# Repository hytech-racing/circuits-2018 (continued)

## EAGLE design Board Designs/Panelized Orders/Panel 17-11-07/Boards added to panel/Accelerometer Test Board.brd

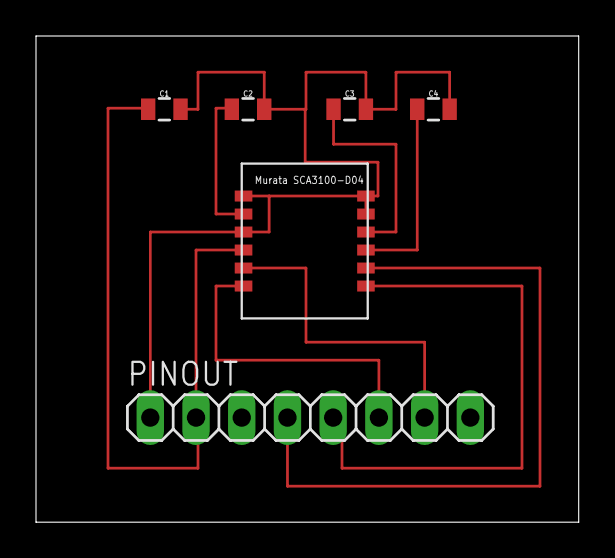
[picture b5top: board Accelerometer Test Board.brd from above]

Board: 2 copper layers, 30.1 x 27.0 mm, 6 parts (0 on the bottom side), 9 nets.

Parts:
C1, C2, C3, C4: 130 nF; 0805
PINOUT: 1X08
U$1: SCA3100-D04

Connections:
GND: C1.2, C2.2, C3.2, C4.2, PINOUT.1, U$1.AVSS, U$1.DVSS, U$1.EMC_GND, U$1.RESERVED
unnamed: C2.1, U$1.A_EXTC
unnamed: C3.1, U$1.D_EXTC
unnamed: C4.1, U$1.DVIO
unnamed: PINOUT.5, U$1.MOSI
unnamed: PINOUT.4, U$1.SCK
unnamed: PINOUT.7, U$1.CSB
unnamed: PINOUT.6, U$1.MISO
VDD: C1.1, PINOUT.2, U$1.VDD

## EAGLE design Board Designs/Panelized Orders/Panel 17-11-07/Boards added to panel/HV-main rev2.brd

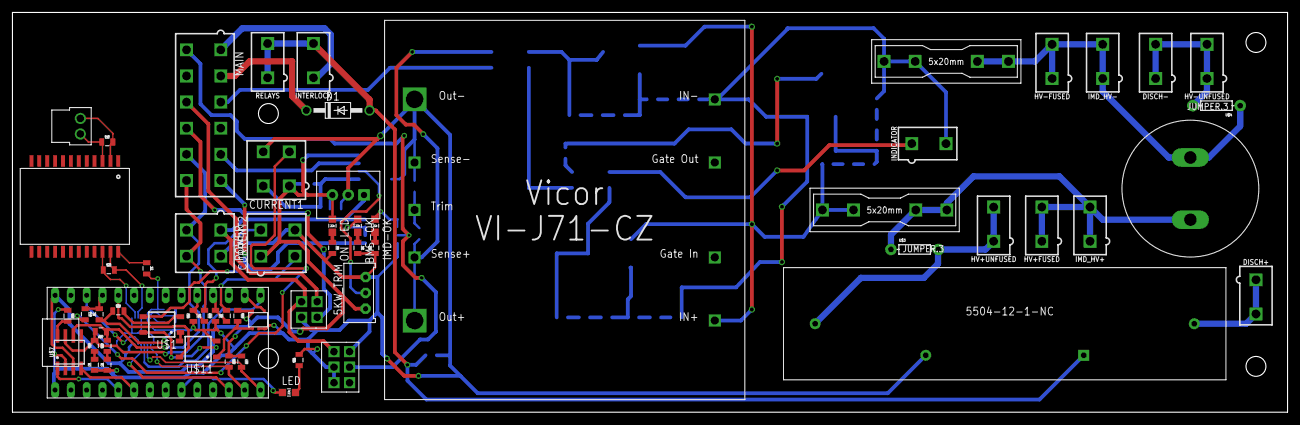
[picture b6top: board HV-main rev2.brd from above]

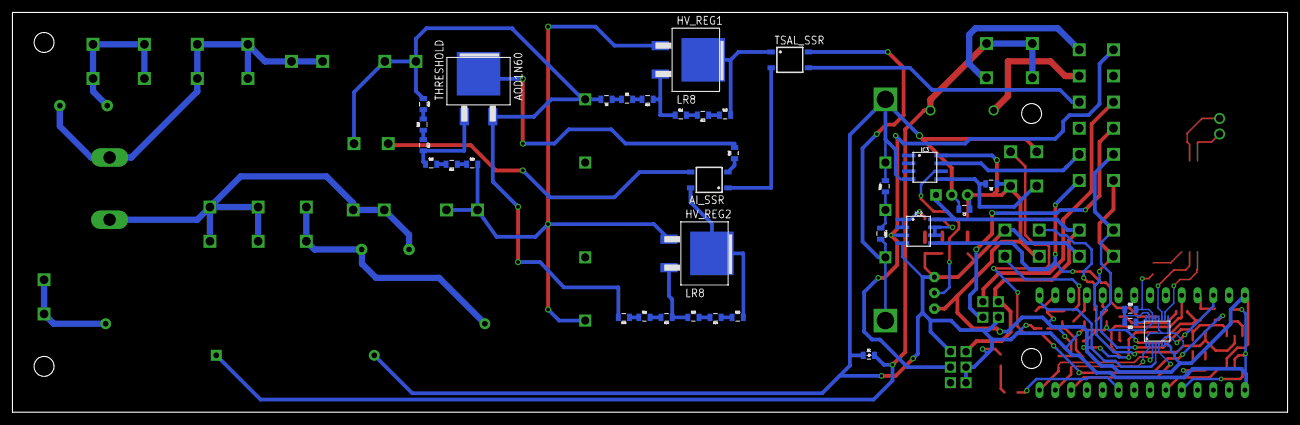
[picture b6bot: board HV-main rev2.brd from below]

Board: 2 copper layers, 205.0 x 64.3 mm, 95 parts (34 on the bottom side), 81 nets.

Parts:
5KW_TRIM: TRIMPOT_3296
AI_SSR: CPC1002N; SOP04
BMS-OK: LED-805
C1: 220uF; LLS2V221MELZ
C3: 1uF; 0805
C4: 27pF; 0805
C8, C9: 560pF; 0805
CURRENT1, CURRENT2: MINIFIT_5566-4
D1: DIODE; DO-41
D2: DIODE0805; 0805_D
DISCH+: DISCHARGE+; MINIFIT_5566-2
DISCH-: DISCHARGE -; MINIFIT_5566-2
EM: CONNECTOR-4; NANO-FIT_VERTICAL-4
FUSE, FUSE1: 1A; 0751.0110
HV+FUSED: MINIFIT_5566-2
HV+UNFUSED: FSAE; MINIFIT_5566-2
HV-FUSED: MINIFIT_5566-2
HV-UNFUSED: FSAE; MINIFIT_5566-2
HV_REG1, HV_REG2: LR8; TO-252
IC1: TO-220
IC2, IC3: NE5532SOIC; SOIC-08
IMD: CONNECTOR-6; NANO-FIT_VERTICAL-6
IMD-OK: LED-805
IMD_HV+: MINIFIT_5566-2
IMD_HV-: MINIFIT_5566-2
INDICATOR: MINIFIT_5566-2
INTERLOCK: MINIFIT_5566-2
ISOSPI: CONNECTOR-2; NANO-FIT_VERTICAL-2
LED: LED-805
MAIN: MINIFIT_5566-12
ON-LED: LED-805
POWER: MINIFIT_5566-4
R1, R2, R26, R30, R33, R34, R44: 1k; 0805
R3, R4, R31: 0805
R5, R28, R29, R40: 100; 0805
R6: 10k; 0805
R7, R11, R12, R13, R23, R24, R25, R32, R36, R37, R43: 2k; 0805
R8, R9, R10: 8.2k; 0805
R14, R15, R16: 500k; 0805
R17, R18, R19: 40k; 0805
R20, R21, R22: 20k; 0805
R27, R35: 120; 0805
R38: 68; 0805
R39: 200; 0805
RELAYS: MINIFIT_5566-2
THRESHOLD: AOD1N60; TO-252
TRIM+: 0805
TRIM-: 0805
TSAL_SSR: CPC1002N; SOP04
U$1, U$11: SOP04
U$2: SM51589PEL
U$3, U$4: JUMPER.3; AXIAL-0.3
U$5: HV_DCDC_VI-J71-CZ
U$7: MCP2551; SOIC-08
U$8: LTC6820; MSOP-16
U$9: TEENSY_3.2_SIMPLE
U$10: STWD100; SOT23-5
U$12: 5504-12-1-NC

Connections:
5KW_TRIG: 5KW_TRIM.2, IC3.6
+3V3: U$8.6, U$9.3.3V
+5V: 5KW_TRIM.1, C3.1, CURRENT1.1, CURRENT2.1, IC1.3, IC3.8, ON-LED.A, R6.1, R36.1, R37.1, R38.1, U$1.4, U$7.3, U$8.1, U$8.7, U$8.8, U$8.9, U$8.12, U$9.VIN, U$10.VCC
+12V: EM.P$1, IC1.1, IC2.8, IMD.P$1, POWER.1
BMS_OK: IC2.5, MAIN.6, U$1.3
BMS_WATCH: U$1.1, U$11.3
BSPD_CUR_FAULT: IC3.7, MAIN.5
CANH: MAIN.12, POWER.4, R27.2, R28.2, U$7.7
CANL: MAIN.11, POWER.3, R27.1, R29.2, U$7.6
CS: U$8.5, U$9.D10(TX2)
CUR_SENSE_1: CURRENT1.2, IC3.5, R6.2
CUR_SENSE_2: R1.1, R32.2, U$9.A3
DISCHARGE1: HV+UNFUSED.1, HV+UNFUSED.2, U$3.P$2, U$12.CONTACT1
DISCHARGE2: DISCH+.1, DISCH+.2, U$12.CONTACT2
DISCHARGE3: DISCH-.1, DISCH-.2, HV-UNFUSED.1, HV-UNFUSED.2, U$4.P$2
EM_IO1: EM.P$3, MAIN.9
EM_IO2: EM.P$4, MAIN.10
GND: 5KW_TRIM.3, C3.2, C4.2, C8.1, C9.1, CURRENT1.4, CURRENT2.4, D2.A, EM.P$2, IC1.2, IC2.4, IC3.4, IMD.P$2, IMD.P$3, IMD.P$4, POWER.2, R3.1, R4.2, R5.2, R7.1, R30.1, R31.2, R32.1, R34.2, R39.1, R43.1, TRIM-.2, U$5.8SENSE-, U$5.9VOUT-, U$7.2, U$8.13, U$8.14, U$9.GND, U$10.EN, U$10.GND, U$11.2, U$12.COIL-
HV+FUSED: C1.P$1, FUSE.L1, FUSE.L2, HV+FUSED.1, HV+FUSED.2, IMD_HV+.1, IMD_HV+.2, U$3.P$1
HV+FUSED_1A: FUSE.R1, FUSE.R2, HV_REG1.1, HV_REG2.1, R14.2, U$5.1VIN+
HV-FUSED: C1.P$2, FUSE1.L1, FUSE1.L2, HV-FUSED.1, HV-FUSED.2, IMD_HV-.1, IMD_HV-.2, U$4.P$1
HV-FUSED_1A: FUSE1.R1, FUSE1.R2, INDICATOR.2, R8.2, R19.1, R20.2, THRESHOLD.3, U$5.4VIN-
ISOSPI-M: ISOSPI.P$2, R40.1, U$2.3
ISOSPI-P: ISOSPI.P$1, R40.2, U$2.2
MISO: R37.2, U$8.3, U$9.D12
MOSI: R36.2, U$8.2, U$9.D11
unnamed: AI_SSR.4, HV_REG2.2(TAB), R25.2
unnamed: HV_REG1.2(TAB), R13.2, TSAL_SSR.1
unnamed: ON-LED.C, R5.1
unnamed: R39.2, U$1.2
unnamed: AI_SSR.2, R26.1
unnamed: AI_SSR.1, TSAL_SSR.2
unnamed: AI_SSR.3, INDICATOR.1
unnamed: R8.1, R9.1
unnamed: R26.2, THRESHOLD.2(TAB)
unnamed: R14.1, R15.1
unnamed: R15.2, R16.2
unnamed: R17.1, R18.1
unnamed: R18.2, R19.2
unnamed: R9.2, R10.2
unnamed: HV_REG2.3, R22.1, R23.1
unnamed: R11.2, R12.2
unnamed: R12.1, R13.1
unnamed: HV_REG1.3, R10.1, R11.1
unnamed: R23.2, R24.2
unnamed: R24.1, R25.1
unnamed: R21.2, R22.2
unnamed: R16.1, R17.2, THRESHOLD.1
unnamed: R20.1, R21.1
unnamed: U$7.1, U$9.D3(CANTX)
unnamed: R30.2, U$7.8
unnamed: C8.2, R28.1
unnamed: C9.2, R29.1
unnamed: LED.C, R31.1
unnamed: CURRENT2.2, R1.2
unnamed: R33.1, U$8.16
unnamed: R33.2, R34.1, U$8.15
unnamed: R35.1, U$2.22, U$8.10
unnamed: R35.2, U$2.23, U$8.11
unnamed: C4.1, U$2.24
unnamed: U$7.4, U$9.D4(CANRX)
unnamed: LED.A, U$9.D7(RX3)
unnamed: R38.2, U$10.WDO, U$11.1
unnamed: U$9.A8, U$11.4
unnamed: IC2.1, IC2.2, IMD-OK.A
unnamed: BMS-OK.A, IC2.6, IC2.7
unnamed: BMS-OK.C, R4.1
unnamed: IMD-OK.C, R3.2
unnamed: U$9.A0, U$10.WDI
unnamed: CURRENT1.3, R44.2
unnamed: CURRENT2.3, R2.2
OKHS: IC2.3, IMD.P$5, MAIN.7
SCK: U$8.4, U$9.D13
SHUTDOWN6: INTERLOCK.1, MAIN.1
SHUTDOWN7: D1.A, D2.C, INTERLOCK.2, RELAYS.1, RELAYS.2, U$12.COIL+
SHUTDOWN7_EXT_OUT: D1.C, MAIN.2
TEMP_SENSE_1: R7.2, R44.1, U$9.A9
TEMP_SENSE_2: R2.1, R43.2, U$9.A2
TRIM: TRIM+.1, TRIM-.1, U$5.7TRIM
TSAL+: MAIN.3, TSAL_SSR.3
TSAL_1: TRIM+.2, TSAL_SSR.4, U$5.5VOUT+, U$5.6SENSE+
